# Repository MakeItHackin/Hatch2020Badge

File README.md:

# Hatch2020Badge

Thank you for being interested in this year's Hudson Alpha Tech Challenge Badge!!!  

View my YouTube video for a quick demo and overview:  
https://www.youtube.com/watch?v=0dqjWGFenuU

The badges were designed by @makeithackin and sponsored by Hudson Alpha.  

More information will come after HATCH weekend.  

The badge is in the shape of the Hudson Alpha logo.  It features a fully functioning circuit if you would like to solder components onto the top surface.  Using a 555 timer and a 4017 Decade Counter, the 10 LEDs will flash one by one.  Using the "speed" switch, the user can either pick a slow or fast blinking mode for the LEDs.  

If you have any questions or comments, please initiate an 'Issue' on github and I will answer as soon as I can.

Below are the components that can be soldered onto the badge for functionality:
CR2032 Battery and Holder
555 Timer
4017 Decade Counter
100 ohm 0805 resistors 
0805 LEDs
Two switches
Two capacitors (for changing speed)
Two 22kohm resistors for 555 timer

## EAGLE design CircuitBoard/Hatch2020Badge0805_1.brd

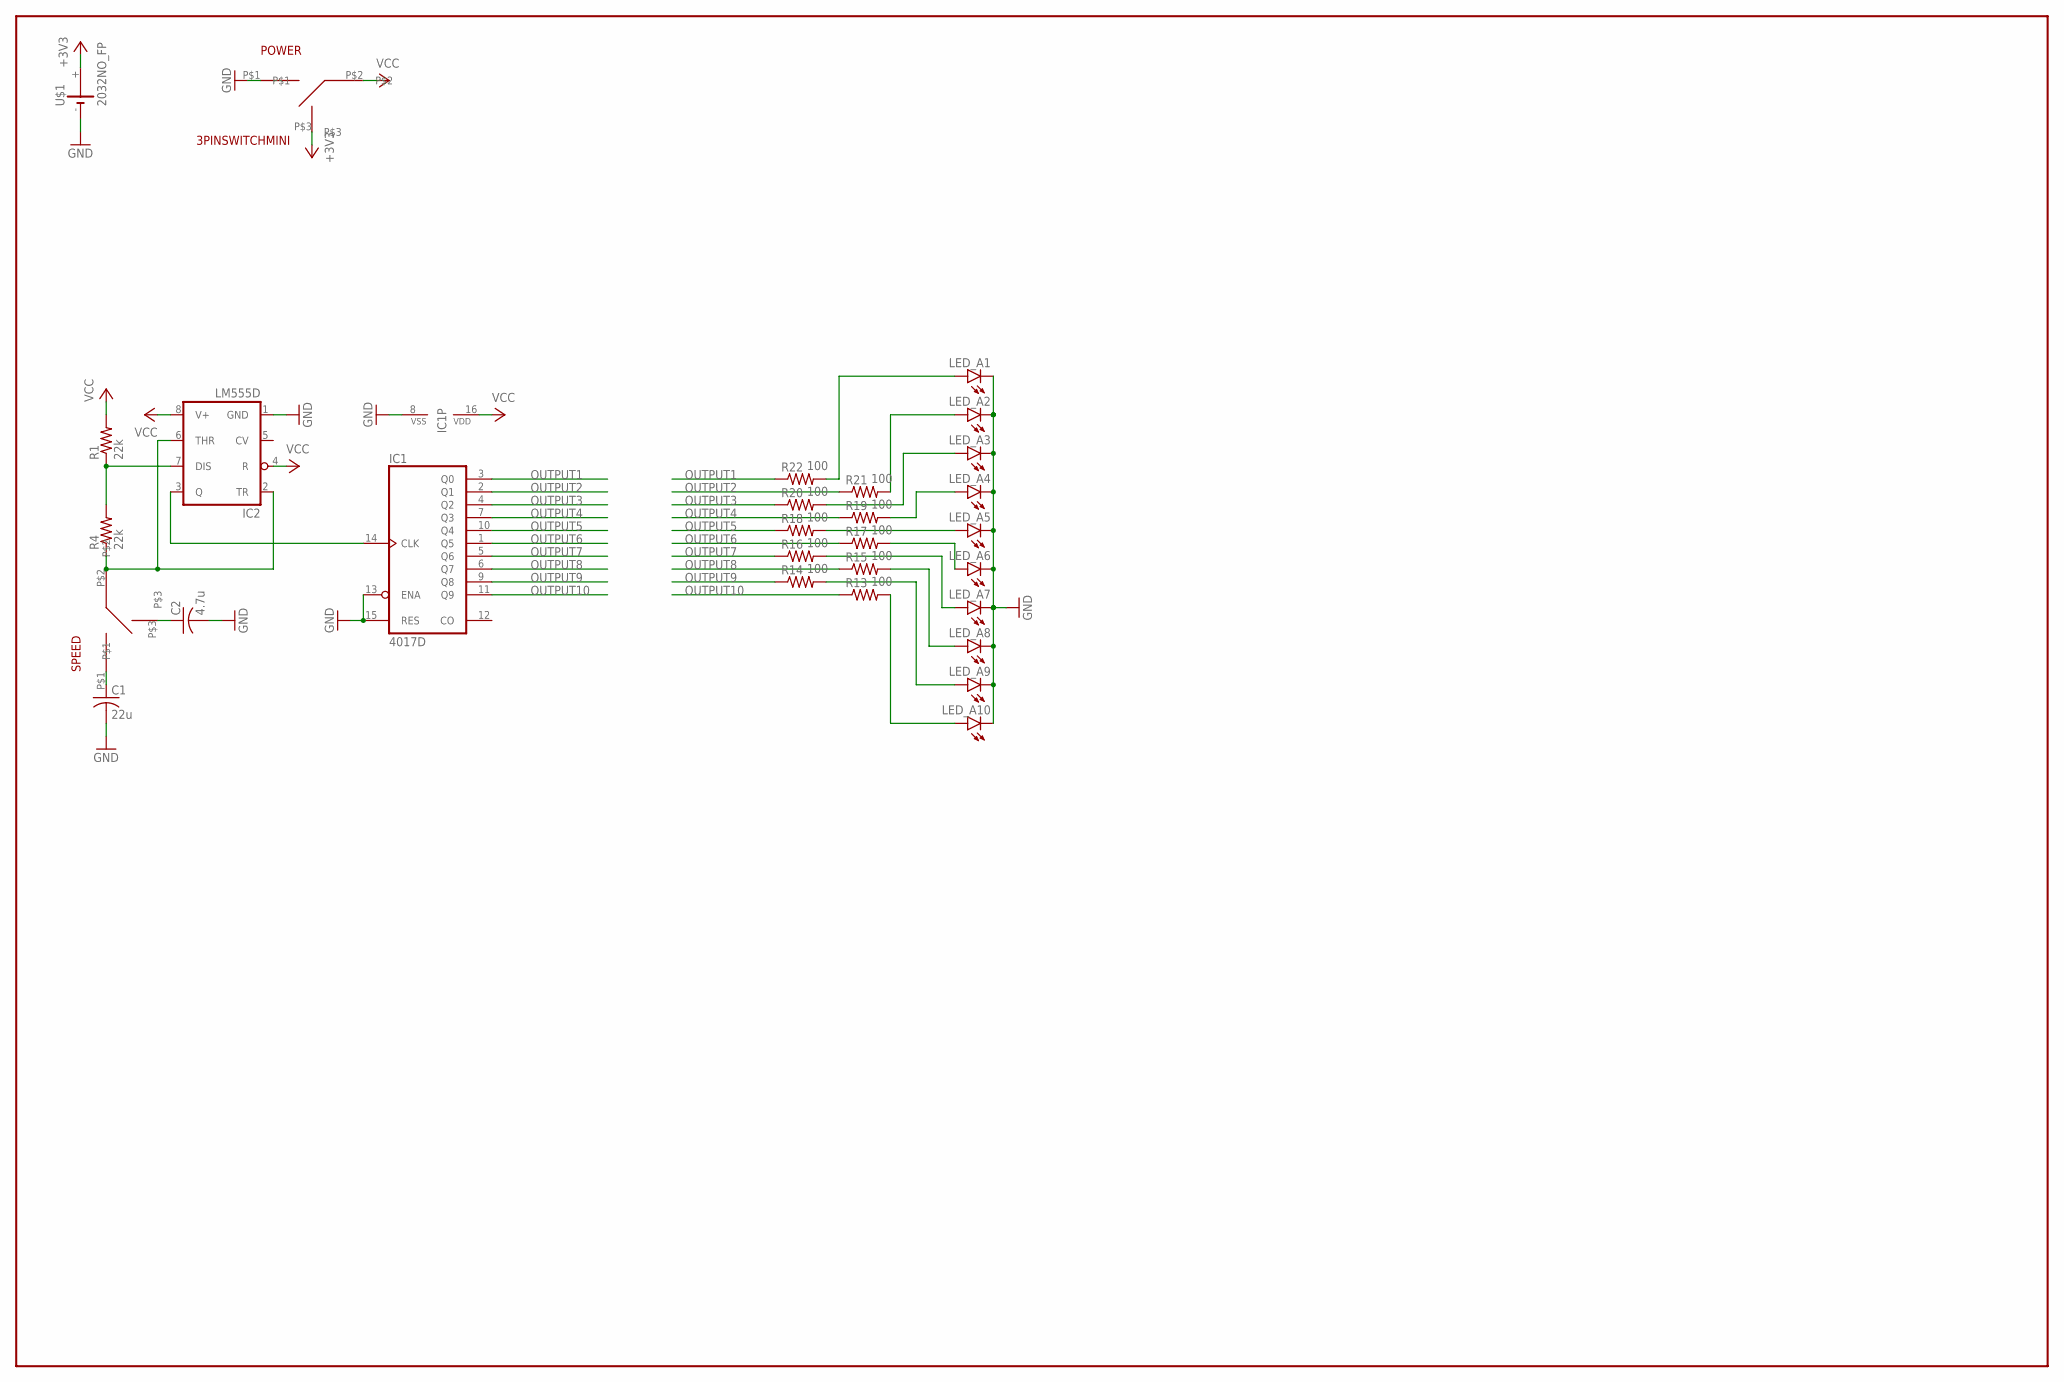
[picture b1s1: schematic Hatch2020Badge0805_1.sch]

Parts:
C1: 22u; C0805
C2: 4.7u; C0805
IC1: 4017D; SO16
IC2: LM555D; SO08
LED_A1, LED_A2, LED_A3, LED_A4, LED_A5, LED_A6, LED_A7, LED_A8, LED_A9, LED_A10: LEDSML0805; SML0805
POWER: 3PINSWITCHMINI; 3PINMINI
R1, R4: 22k; R0805
R13, R14, R15, R16, R17, R18, R19, R20, R21, R22: 100; R0805
SPEED: 3PINSWITCHMINI; 3PINMINI
U$1: 2032NO_FP; 2032_NO_FP

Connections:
+3V3: POWER.P$3, U$1.+
GND: C1.2, C2.2, IC1.8 (VSS), IC1.13 (ENA), IC1.15 (RES), IC2.1 (GND), LED_A1.C, LED_A2.C, LED_A3.C, LED_A4.C, LED_A5.C, LED_A6.C, LED_A7.C, LED_A8.C, LED_A9.C, LED_A10.C, POWER.P$1, U$1.-
unnamed: IC2.7 (DIS), R1.1, R4.2
unnamed: LED_A2.A, R21.2
unnamed: LED_A3.A, R20.2
unnamed: C1.1, SPEED.P$1
unnamed: C2.1, SPEED.P$3
unnamed: LED_A1.A, R22.2
unnamed: LED_A4.A, R19.2
unnamed: LED_A5.A, R18.2
unnamed: LED_A6.A, R17.2
unnamed: LED_A7.A, R16.2
unnamed: LED_A8.A, R15.2
unnamed: LED_A9.A, R14.2
unnamed: LED_A10.A, R13.2
unnamed: IC2.2 (TR), IC2.6 (THR), R4.1, SPEED.P$2
unnamed: IC1.14 (CLK), IC2.3 (Q)
OUTPUT1: IC1.3 (Q0), R22.1
OUTPUT2: IC1.2 (Q1), R21.1
OUTPUT3: IC1.4 (Q2), R20.1
OUTPUT4: IC1.7 (Q3), R19.1
OUTPUT5: IC1.10 (Q4), R18.1
OUTPUT6: IC1.1 (Q5), R17.1
OUTPUT7: IC1.5 (Q6), R16.1
OUTPUT8: IC1.6 (Q7), R15.1
OUTPUT9: IC1.9 (Q8), R14.1
OUTPUT10: IC1.11 (Q9), R13.1
VCC: IC1.16 (VDD), IC2.4 (R), IC2.8 (V+), POWER.P$2, R1.2

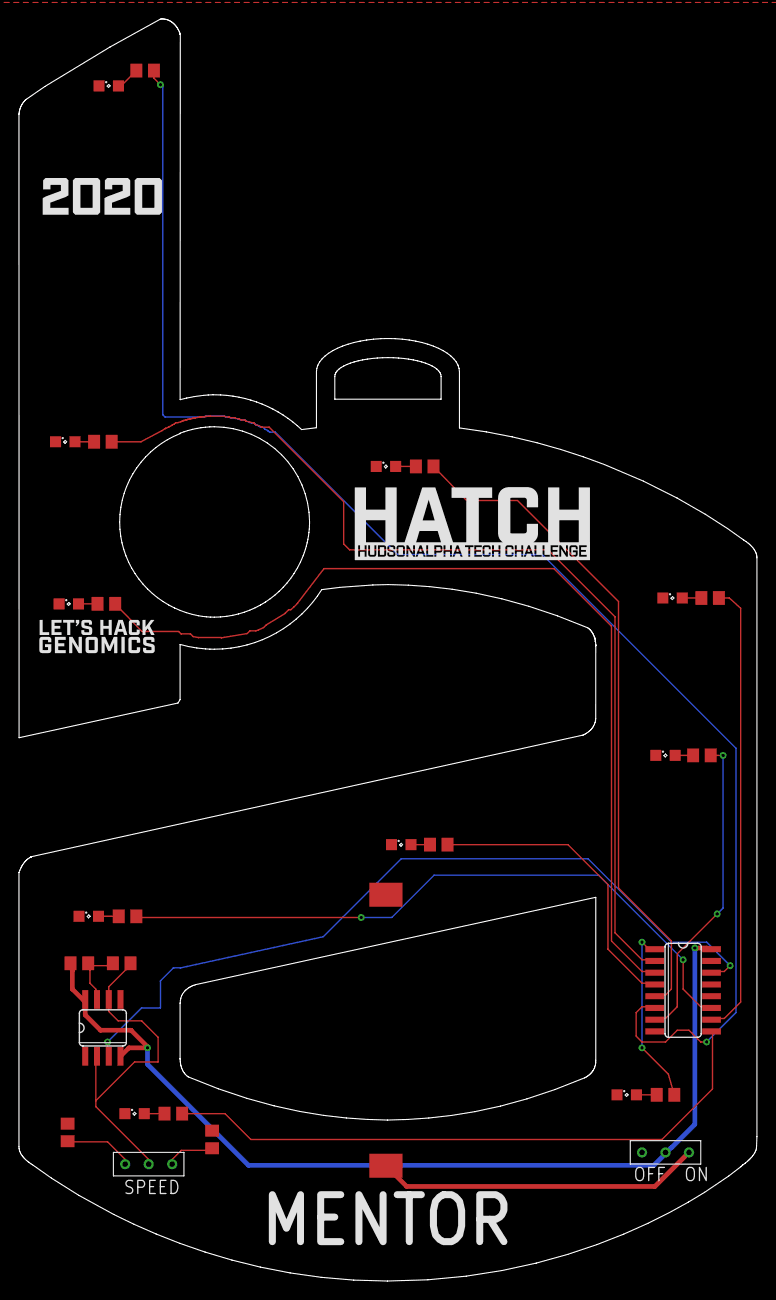
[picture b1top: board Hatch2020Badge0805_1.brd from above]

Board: 2 copper layers, 79.8 x 136.5 mm, 29 parts (0 on the bottom side), 28 nets.

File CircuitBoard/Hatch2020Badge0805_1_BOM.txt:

Partlist exported from C:/Users/Andrew/Documents/EAGLE/projects/HATCH2020Badge/Hatch2020Badge0805_1.sch at 3/8/2020 4:19 PM

Part    Value          Device         Package    Description                POPULARITY SPICEPREFIX
C1      22u            C-USC0805      C0805      CAPACITOR, American symbol 63         C          
C2      4.7u           C-USC0805      C0805      CAPACITOR, American symbol 63         C          
IC1     4017D          4017D          SO16       COUNTER/DIVIDER            0                     
IC2     LM555D         LM555D         SO08       TIMER                                            
LED_A1                 LEDSML0805     SML0805    LED                        17                    
LED_A2                 LEDSML0805     SML0805    LED                        17                    
LED_A3                 LEDSML0805     SML0805    LED                        17                    
LED_A4                 LEDSML0805     SML0805    LED                        17                    
LED_A5                 LEDSML0805     SML0805    LED                        17                    
LED_A6                 LEDSML0805     SML0805    LED                        17                    
LED_A7                 LEDSML0805     SML0805    LED                        17                    
LED_A8                 LEDSML0805     SML0805    LED                        17                    
LED_A9                 LEDSML0805     SML0805    LED                        17                    
LED_A10                LEDSML0805     SML0805    LED                        17                    
POWER   3PINSWITCHMINI 3PINSWITCHMINI 3PINMINI                                                    
R1      22k            R-US_R0805     R0805      RESISTOR, American symbol  85         R          
R4      22k            R-US_R0805     R0805      RESISTOR, American symbol  85         R          
R13     100            R-US_R0805     R0805      RESISTOR, American symbol  85         R          
R14     100            R-US_R0805     R0805      RESISTOR, American symbol  85         R          
R15     100            R-US_R0805     R0805      RESISTOR, American symbol  85         R          
R16     100            R-US_R0805     R0805      RESISTOR, American symbol  85         R          
R17     100            R-US_R0805     R0805      RESISTOR, American symbol  85         R          
R18     100            R-US_R0805     R0805      RESISTOR, American symbol  85         R          
R19     100            R-US_R0805     R0805      RESISTOR, American symbol  85         R          
R20     100            R-US_R0805     R0805      RESISTOR, American symbol  85         R          
R21     100            R-US_R0805     R0805      RESISTOR, American symbol  85         R          
R22     100            R-US_R0805     R0805      RESISTOR, American symbol  85         R          
SPEED   3PINSWITCHMINI 3PINSWITCHMINI 3PINMINI                                                    
U$1     2032NO_FP      2032NO_FP      2032_NO_FP
